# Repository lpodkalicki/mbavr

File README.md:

# MBAVR
Family of minimalist development boards for AVR microcontrollers.

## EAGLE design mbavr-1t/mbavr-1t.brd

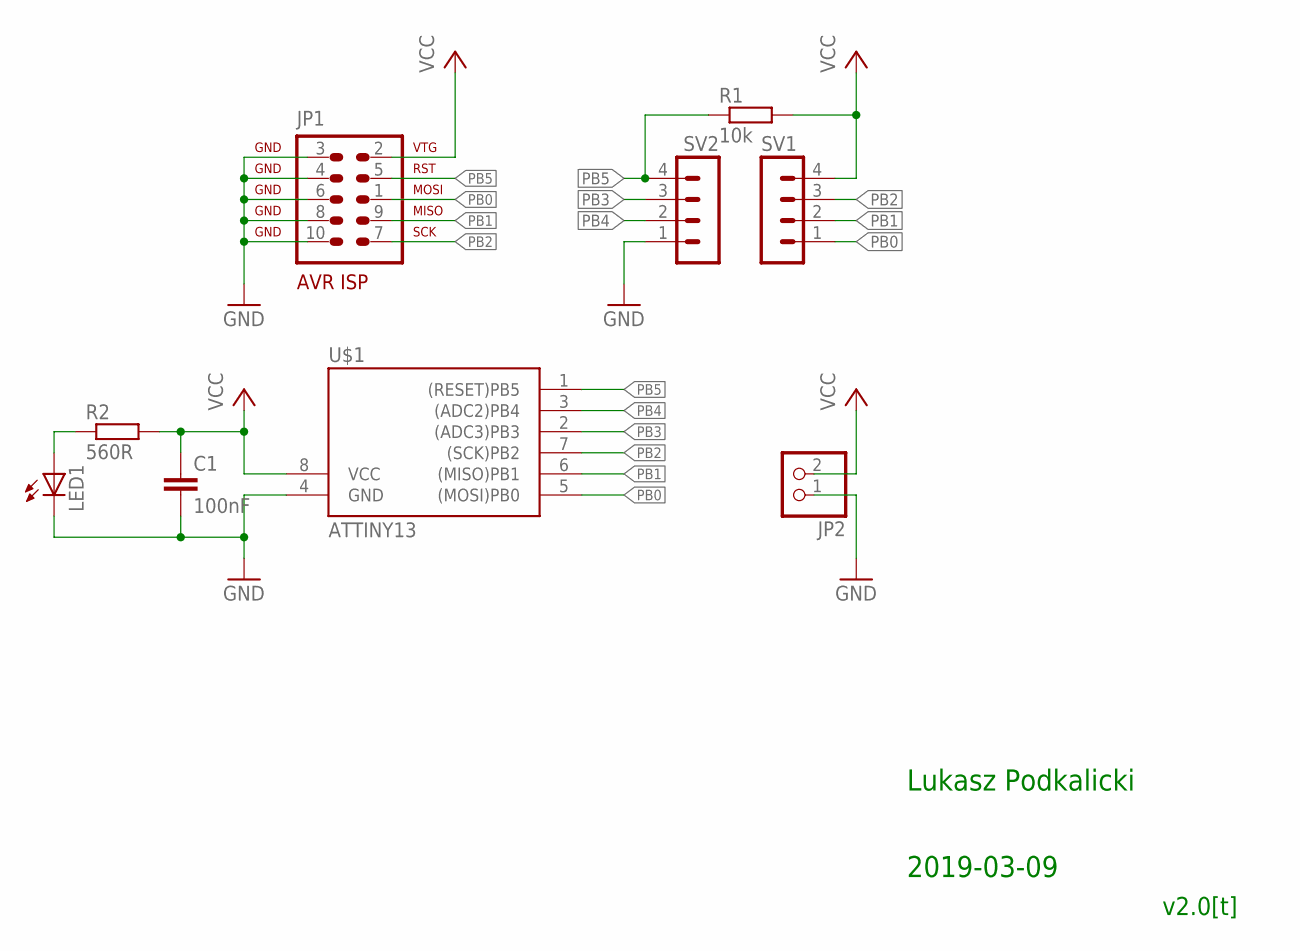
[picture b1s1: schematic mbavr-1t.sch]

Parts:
C1: 100nF; C1206K
JP1: AVR-ISP-10
JP2: PINHD-1X2; 1X02
LED1: LEDSML1206; SML1206
R1: 10k; R1206
R2: 560R; R1206
SV1, SV2: MA04-1
U$1: ATTINY13; DIL08

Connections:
GND: C1.2, JP1.3, JP1.4, JP1.6, JP1.8, JP1.10, JP2.1, LED1.C, SV2.1, U$1.4 (GND)
unnamed: LED1.A, R2.1
PB0: JP1.1, SV1.1, U$1.5 ((MOSI)PB0)
PB1: JP1.9, SV1.2, U$1.6 ((MISO)PB1)
PB2: JP1.7, SV1.3, U$1.7 ((SCK)PB2)
PB3: SV2.3, U$1.2 ((ADC3)PB3)
PB4: SV2.2, U$1.3 ((ADC2)PB4)
PB5: JP1.5, R1.1, SV2.4, U$1.1 ((RESET)PB5)
VCC: C1.1, JP1.2, JP2.2, R1.2, R2.2, SV1.4, U$1.8 (VCC)

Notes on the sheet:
Lukasz Podkalicki
2019-03-09
v2.0[t]

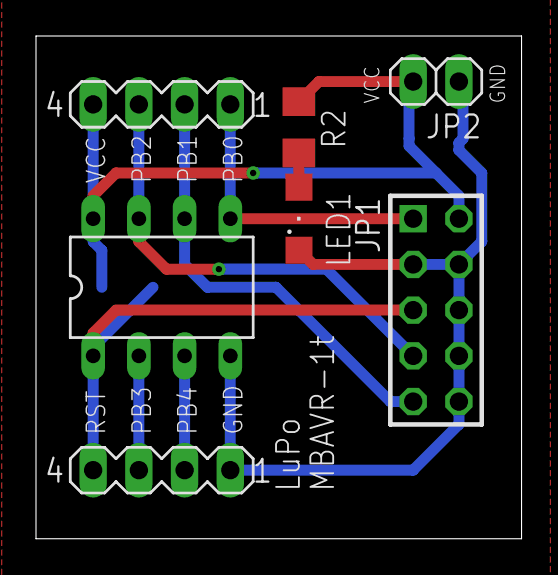
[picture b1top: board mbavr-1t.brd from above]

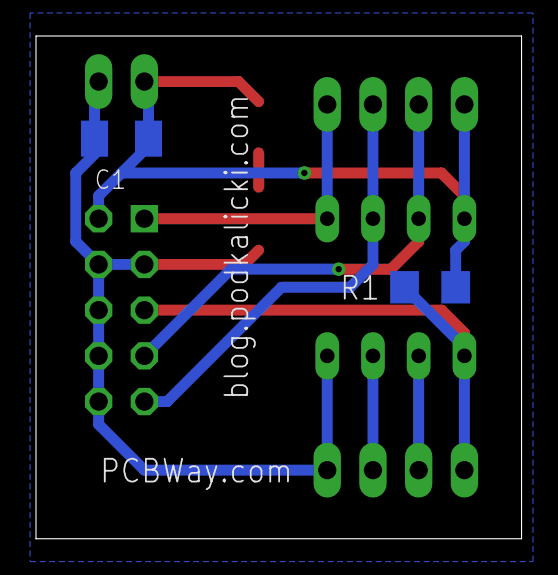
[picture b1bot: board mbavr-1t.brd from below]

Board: 2 copper layers, 27.0 x 27.9 mm, 9 parts (2 on the bottom side), 9 nets.

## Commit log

2019-03-09 Add schematic and board design for MBAVR-1t (ATtiny13, ATtiny25, ATtiny45, ATtiny85).
2019-03-09 Update README.
2019-03-09 Add top and bottom layer image.
2019-03-19 Update R2 value.
